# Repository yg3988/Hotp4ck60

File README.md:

# Hotp4ck 60 - 60% Layout Custom Keyboard Schematic & PCB

This keyboard PCB is a ANSI 60% Layout with Bluetooth 5.4 support using the [nRF52840](https://www.nordicsemi.com/products/nrf52840) chip produced by [Nordic Semiconductor](https://www.nordicsemi.com/).

## Features

* Supported Bluetooth
* USB Type-C
* 1000mAh Li-Po Battery
    * Battery Connector : MOLEX [51021-0200](https://www.molex.com/en-us/products/part-detail/510210200)
    * Battery Connector Socket : MOLEX [PicoBlade 53261-0271](https://www.molex.com/en-us/products/part-detail/532610271)
    * Note :
        * If you change the battery capacity, You MUST program the battery chargin current by replacing `R4` at this [Schematic](/Hotp4ck_Battery.kicad_sch) for safety.
* No LED per key 
* No Underglow LEDs
* Split Space-bar(1.25u + 2.75u + 2.25u)

## Schematic

* [PDF Schematic](misc/Hotp4ck60_schemetic.pdf)

## PCB

Generated by [InteractiveHtmlBom](https://github.com/openscopeproject/InteractiveHtmlBom) plugin for KiCad.

## Keyboard Layout

## Bootloader & Firmware

* [Bootloader](https://github.com/yg3988/Adafruit_nRF52_Bootloader/actions)
    * Download Bootloader from the Recently `Actions/Artifacts`

* [Firmware](https://github.com/yg3988/zmk-config/actions/runs/5494728345)
    * Download Firmware from the Recently `Actions/Artifacts`
 
## License
This keyboard PCB is licensed under the CERN Open Hardware Licence Version 2 - Permissive.

## References

* ### PCB Design : [zmk-designguide](https://github.com/ebastler/zmk-designguide) by [ebastler](https://github.com/ebastler)
* ### Firmware
    * ### ZMK : [zmk](https://github.com/zhiayang/zmk) by [zhiayang](https://github.com/zhiayang)
        > Source ZMK : zmkfirmware's [zmk](https://github.com/zmkfirmware/zmk)
    * ### [zmk-config](https://zmk.dev/docs/user-setup)
* ### Bootloader : [Adafruit_nRF52_Bootloader](https://github.com/adafruit/Adafruit_nRF52_Bootloader)

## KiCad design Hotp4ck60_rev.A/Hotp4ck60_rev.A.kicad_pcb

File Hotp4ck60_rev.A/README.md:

# Hotp4ck 60 - 60% Layout Custom Keyboard Schematic & PCB

This keyboard PCB is a ANSI 60% Layout with Bluetooth 5.4 support using the [nRF52840](https://www.nordicsemi.com/products/nrf52840) chip produced by [Nordic Semiconductor](https://www.nordicsemi.com/).

## Features

* Supported Bluetooth
* USB Type-C
* 1000mAh Li-Po Battery
    * Battery Connector : MOLEX [51021-0200](https://www.molex.com/en-us/products/part-detail/510210200)
    * Battery Connector Socket : MOLEX [PicoBlade 53261-0271](https://www.molex.com/en-us/products/part-detail/532610271)
    * Note :
        * If you change the battery capacity, You MUST program the battery chargin current by replacing `R4` at this [Schematic](/Hotp4ck_Battery.kicad_sch) for safety.
* No LED per key 
* No Underglow LEDs
* Split Space-bar(1.25u + 2.75u + 2.25u)

## Schematic

* [PDF Schematic](misc/Hotp4ck60_schemetic.pdf)

## PCB

Generated by [InteractiveHtmlBom](https://github.com/openscopeproject/InteractiveHtmlBom) plugin for KiCad.

## Keyboard Layout

## Bootloader & Firmware

* [Bootloader](https://github.com/yg3988/Adafruit_nRF52_Bootloader/actions)
    * Download Bootloader from the Recently `Actions/Artifacts`

* [Firmware](https://github.com/yg3988/zmk-config/actions/)
    * Download Firmware from the Recently `Actions/Artifacts`
 
## License
This keyboard PCB is licensed under the CERN Open Hardware Licence Version 2 - Permissive.

## References

* ### PCB Design : [zmk-designguide](https://github.com/ebastler/zmk-designguide) by [ebastler](https://github.com/ebastler)
* ### Firmware
    * ### ZMK : [zmk](https://github.com/zhiayang/zmk) by [zhiayang](https://github.com/zhiayang)
        > Source ZMK : zmkfirmware's [zmk](https://github.com/zmkfirmware/zmk)
    * ### [zmk-config](https://zmk.dev/docs/user-setup)
* ### Bootloader : [Adafruit_nRF52_Bootloader](https://github.com/adafruit/Adafruit_nRF52_Bootloader)

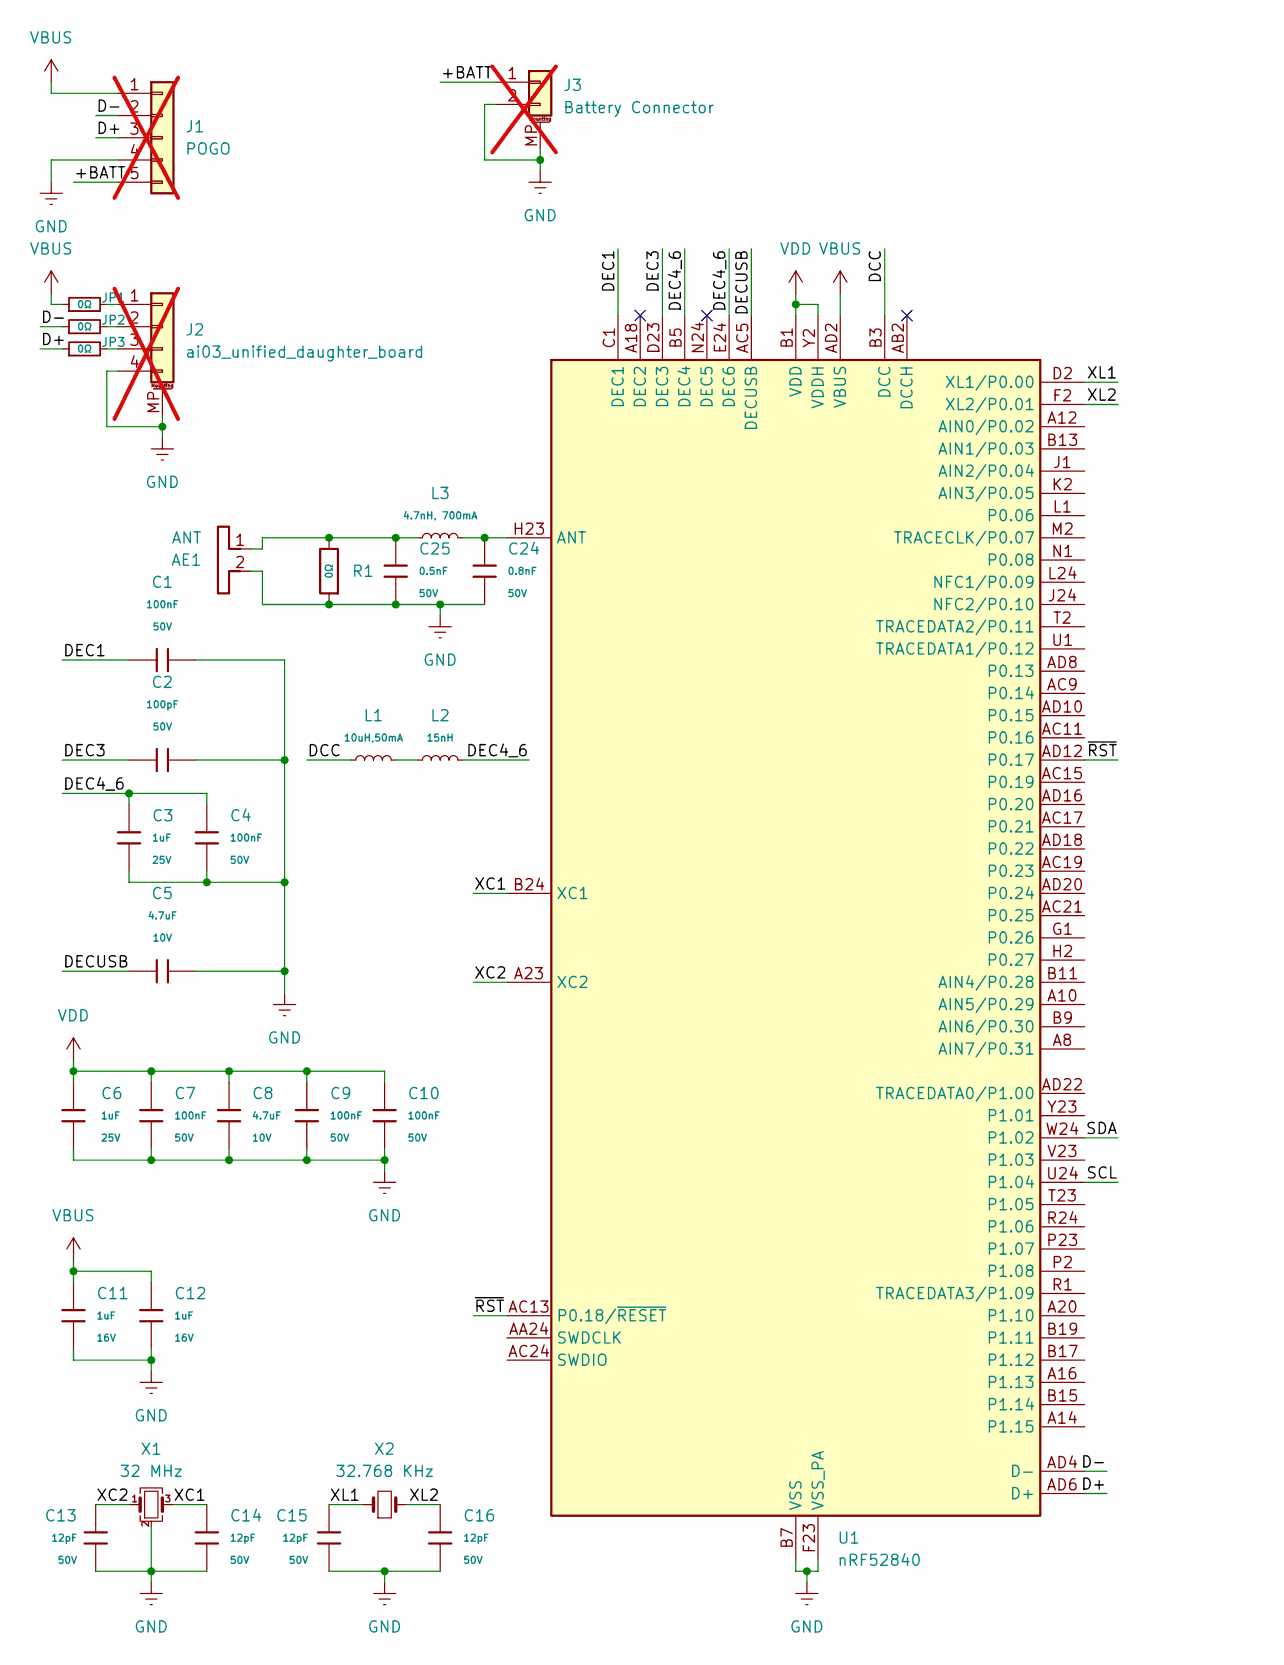
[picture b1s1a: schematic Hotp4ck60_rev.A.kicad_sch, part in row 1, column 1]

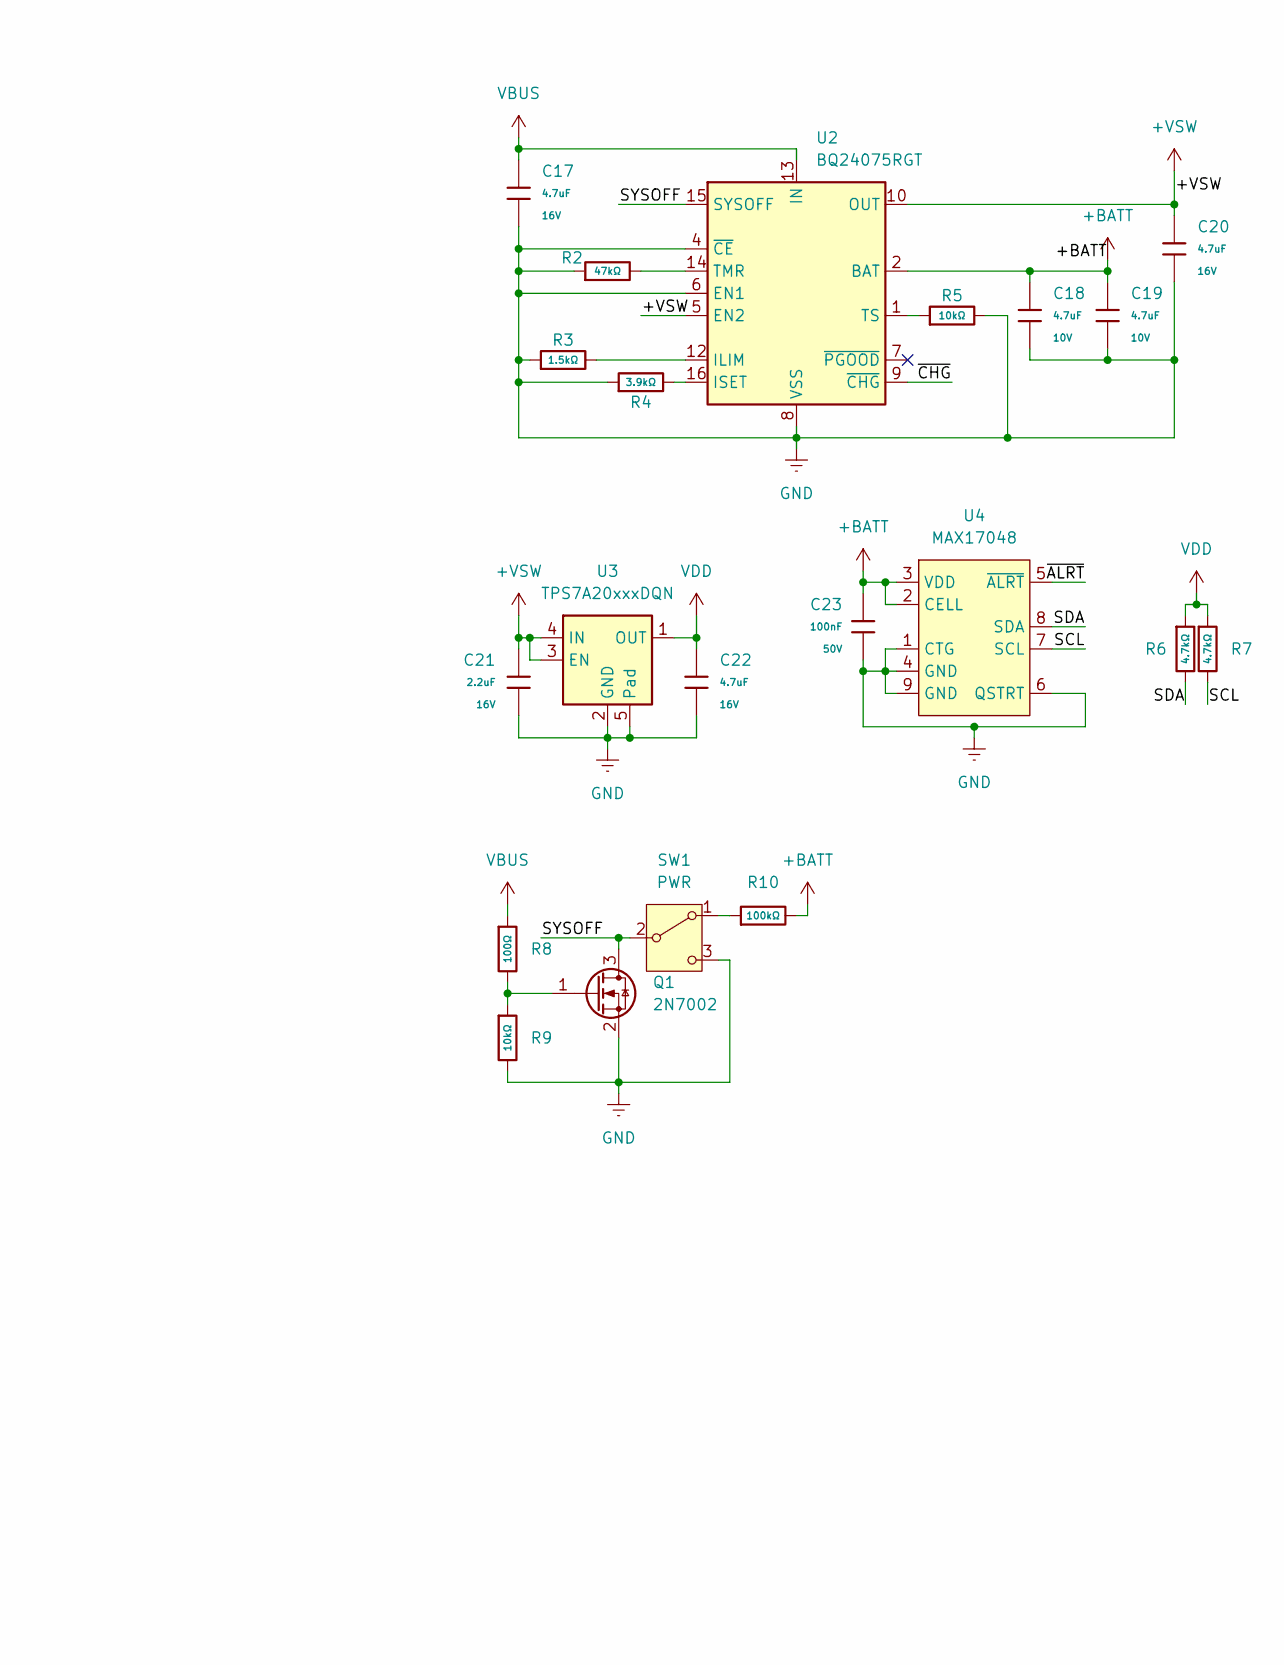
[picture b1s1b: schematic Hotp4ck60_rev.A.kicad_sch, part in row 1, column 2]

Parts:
AE1: ANT; Texas_SWRA117D_2.4GHz_Right
C1, C4, C7, C9, C10, C23: 100nF; C_0402_1005Metric; Voltage Rated 50V; Tolerance ±10%; Part CL05B104KB54PNC; LCSC C307331
C2: 100pF; C_0402_1005Metric; Voltage Rated 50V; Tolerance ±5%; Part 0402CG101J500NT; LCSC C1546
C3, C6: 1uF; C_0402_1005Metric; Voltage Rated 25V; Tolerance ±10%; Part CL05A105KA5NQNC; LCSC C52923
C5, C8, C18, C19: 4.7uF; C_0402_1005Metric; Voltage Rated 10V; Tolerance ±20%; Part CL05A475MP5NRNC; LCSC C23733
C11, C12: 1uF; C_0402_1005Metric; Voltage Rated 16V; Tolerance ±10%; Part CL10A105KO8NNNC; LCSC C1592
C13, C14, C15, C16: 12pF; C_0402_1005Metric; Voltage Rated 50V; Tolerance ±5%; Part 0402CG120J500NT; LCSC C1547
C17, C20, C22: 4.7uF; C_0603_1608Metric; Voltage Rated 16V; Tolerance ±10%; Part CL10A475KO8NNNC; LCSC C19666
C21: 2.2uF; C_0603_1608Metric; Voltage Rated 16V; Tolerance ±10%; Part CL10A225KO8NNNC; LCSC C23630
C24: 0.8nF; C_0402_1005Metric; Voltage Rated 50V; Tolerance ±0.05pF; Part GJM1555C1HR80WB01D; LCSC C88902
C25: 0.5nF; C_0402_1005Metric; Voltage Rated 50V; Tolerance ±0.1pF; Part CC0402BRNPO9BNR50; LCSC C309456
J1: POGO; PinHeader_1x05_P2.54mm_Vertical; not fitted
J2: ai03_unified_daughter_board; JST_SH_SM04B-SRSS-TB_1x04-1MP_P1.00mm_Horizontal; not fitted
J3: Battery Connector; Molex_PicoBlade_53261-0271_1x02-1MP_P1.25mm_Horizontal; not fitted
JP1, JP2, JP3: 0Ω; R_0201_0603Metric
L1: 10uH,50mA; L_0603_1608Metric; Tolerance ±20%; Part APQM18FN100M00D; LCSC C50325679
L2: 15nH; L_0402_1005Metric; Tolerance ±5%; Part VHF100505HQ15NJT; LCSC C395049
L3: 4.7nH, 700mA; L_0402_1005Metric; Tolerance ±0.3nH; Part VHF100505HQ4N7ST; LCSC C395070
Q1: 2N7002; SOT-23
R1: 0Ω; R_0402_1005Metric; Overload Voltage (Max) 50V; Tolerance ±1%; Part 0402WGF0000TCE; LCSC C17168
R2: 47kΩ; R_0402_1005Metric; Overload Voltage (Max) 50V; Tolerance ±1%; Part 0402WGF4702TCE; LCSC C25792
R3: 1.5kΩ; R_0402_1005Metric; Overload Voltage (Max) 50V; Tolerance ±1%; Part 0402WGF1501TCE; LCSC C25867
R4: 3.9kΩ; R_0402_1005Metric; Overload Voltage (Max) 50V; Tolerance ±1%; Part 0402WGF3901TCE; LCSC C51721
R5, R9: 10kΩ; R_0402_1005Metric; Overload Voltage (Max) 50V; Tolerance ±1%; Part 0402WGF1002TCE; LCSC C25744
R6, R7: 4.7kΩ; R_0402_1005Metric; Overload Voltage (Max) 50V; Tolerance ±1%; Part 0402WGF4701TCE; LCSC C25900
R8: 100Ω; R_0402_1005Metric; Overload Voltage (Max) 50V; Tolerance ±1%; Part 0402WGF1000TCE; LCSC C25076
R10: 100kΩ; R_0402_1005Metric; Overload Voltage (Max) 50V; Tolerance ±1%; Part 0402WGF1003TCE; LCSC C25741
SW1: PWR; SW-SMD_SHOUHAN_MST-22D18G23J_C2875122
U1: nRF52840; Nordic_AQFN-73-1EP_7x7mm_P0.5mm
U2: BQ24075RGT; VQFN-16-1EP_3x3mm_P0.5mm_EP1.6x1.6mm
U3: TPS7A20xxxDQN; Texas_X2SON-4_1x1mm_P0.65mm
U4: MAX17048; DFN-8-1EP_2x2mm_P0.5mm_EP0.6x1.2mm
X1: 32 MHz; Crystal_SMD_2016-4Pin_2.0x1.6mm
X2: 32.768 KHz; Crystal_SMD_2012-2Pin_2.0x1.2mm

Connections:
+BATT: C18.2, C19.2, C23.1, J1.5, J3.1, R10.2, U2.2 (BAT), U2.3 (BAT), U4.2 (CELL), U4.3 (VDD)
+VSW: C20.1, C21.1, U2.5 (EN2), U2.10 (OUT), U2.11 (OUT), U3.3 (EN), U3.4 (IN)
/D+: J1.3, JP3.1, U1.AD6 (D+)
/D-: J1.2, JP2.1, U1.AD4 (D-)
/DCC: L1.1, U1.B3 (DCC)
/DEC1: C1.1, U1.C1 (DEC1)
/DEC3: C2.1, U1.D23 (DEC3)
/DEC4_6: C3.1, C4.1, L2.2, U1.B5 (DEC4), U1.E24 (DEC6)
/DECUSB: C5.2, U1.AC5 (DECUSB)
/SCL: R7.2, U1.U24 (P1.04), U4.7 (SCL)
/SDA: R6.2, U1.W24 (P1.02), U4.8 (SDA)
/SYSOFF: Q1.3 (D), SW1.2 (B), U2.15 (SYSOFF)
/XC1: C14.1, U1.B24 (XC1), X1.3
/XC2: C13.1, U1.A23 (XC2), X1.1
/XL1: C15.1, U1.D2 (XL1/P0.00), X2.1
/XL2: C16.1, U1.F2 (XL2/P0.01), X2.2
/~ALRT: U4.5 (~ALRT)
/~CHG: U2.9 (~CHG)
/~RST: U1.AC13 (P0.18/~RESET), U1.AD12 (P0.17)
GND: AE1.2, C1.2, C2.2, C3.2, C4.2, C5.1, C6.1, C7.1, C8.1, C9.1, C10.1, C11.1, C12.1, C13.2, C14.2, C15.2, C16.2, C17.2, C18.1, C19.1, C20.2, C21.2, C22.2, C23.2, C24.1, C25.1, J1.4, J2.4, J2.MP (MountPin), J3.2, J3.MP (MountPin), Q1.2 (S), R1.1, R2.1, R3.1, R4.1, R5.2, R9.2, SW1.3 (C), U1.B7 (VSS), U1.EP (VSS), U1.F23 (VSS_PA), U2.4 (~CE), U2.6 (EN1), U2.8 (VSS), U2.17 (VSS), U3.2 (GND), U3.5 (Pad), U4.1 (CTG), U4.4 (GND), U4.6 (QSTRT), U4.9 (GND), X1.2 (G), X1.4 (G)
unnamed: AE1.1, C25.2, L3.1, R1.2
unnamed: J2.1, JP1.2
unnamed: J2.2, JP2.2
unnamed: J2.3, JP3.2
unnamed: L1.2, L2.1
unnamed: Q1.1 (G), R8.2, R9.1
unnamed: R10.1, SW1.1 (A)
unnamed: C24.2, L3.2, U1.H23 (ANT)
unnamed: R3.2, U2.12 (ILIM)
unnamed: R4.2, U2.16 (ISET)
unnamed: R2.2, U2.14 (TMR)
unnamed: R5.1, U2.1 (TS)
VBUS: C11.2, C12.2, C17.1, J1.1, JP1.1, R8.1, U1.AD2 (VBUS), U2.13 (IN)
VDD: C6.2, C7.2, C8.2, C9.2, C10.2, C22.1, R6.1, R7.1, U1.A22 (VDD), U1.AD14 (VDD), U1.AD23 (VDD), U1.B1 (VDD), U1.W1 (VDD), U1.Y2 (VDDH), U3.1 (OUT)

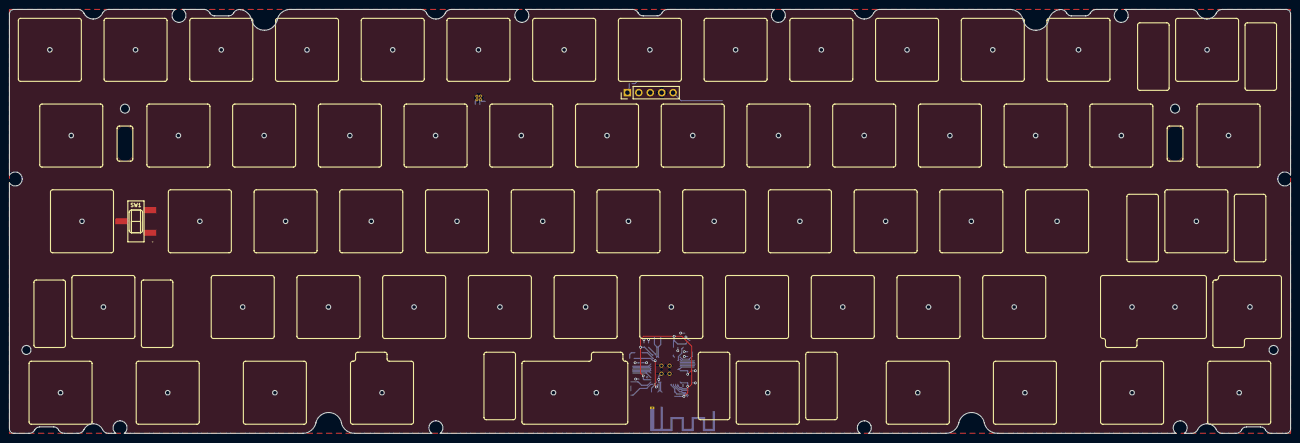
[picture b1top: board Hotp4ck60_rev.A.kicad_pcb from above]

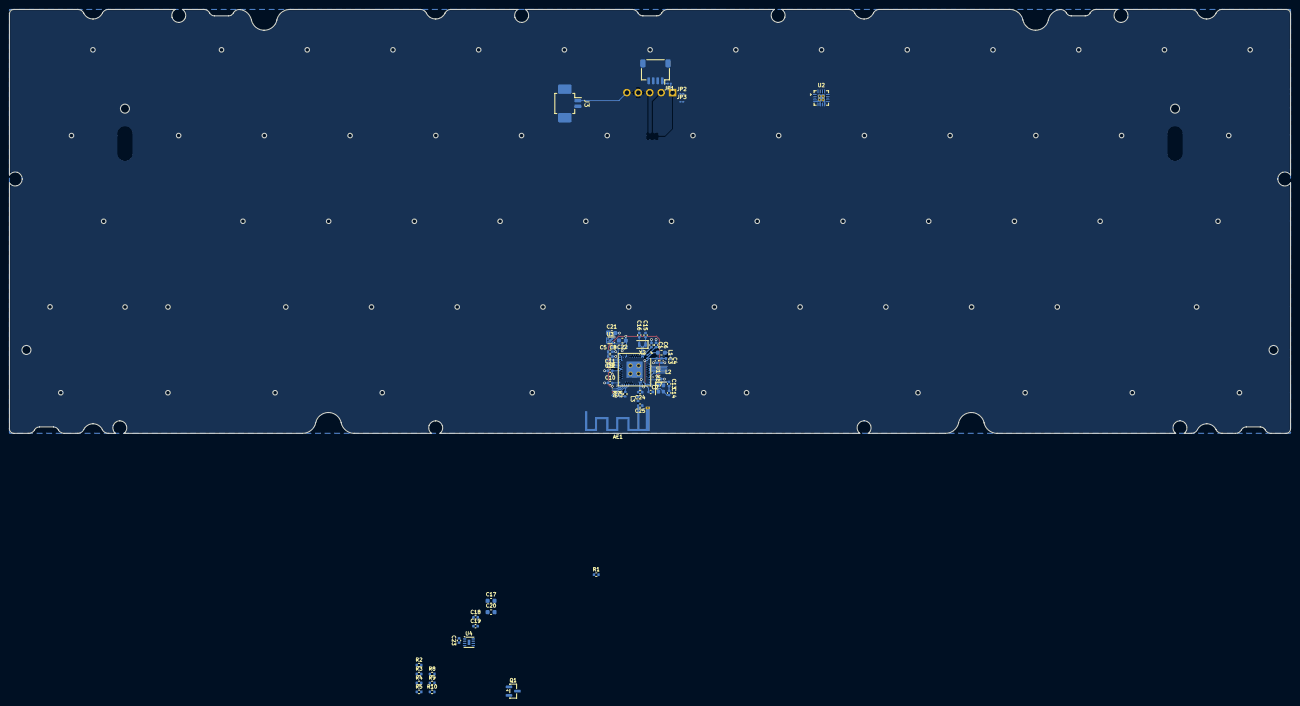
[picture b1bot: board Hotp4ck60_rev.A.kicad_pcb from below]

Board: 2 copper layers, 284.7 x 94.2 mm, 53 parts (51 on the bottom side), 32 nets.

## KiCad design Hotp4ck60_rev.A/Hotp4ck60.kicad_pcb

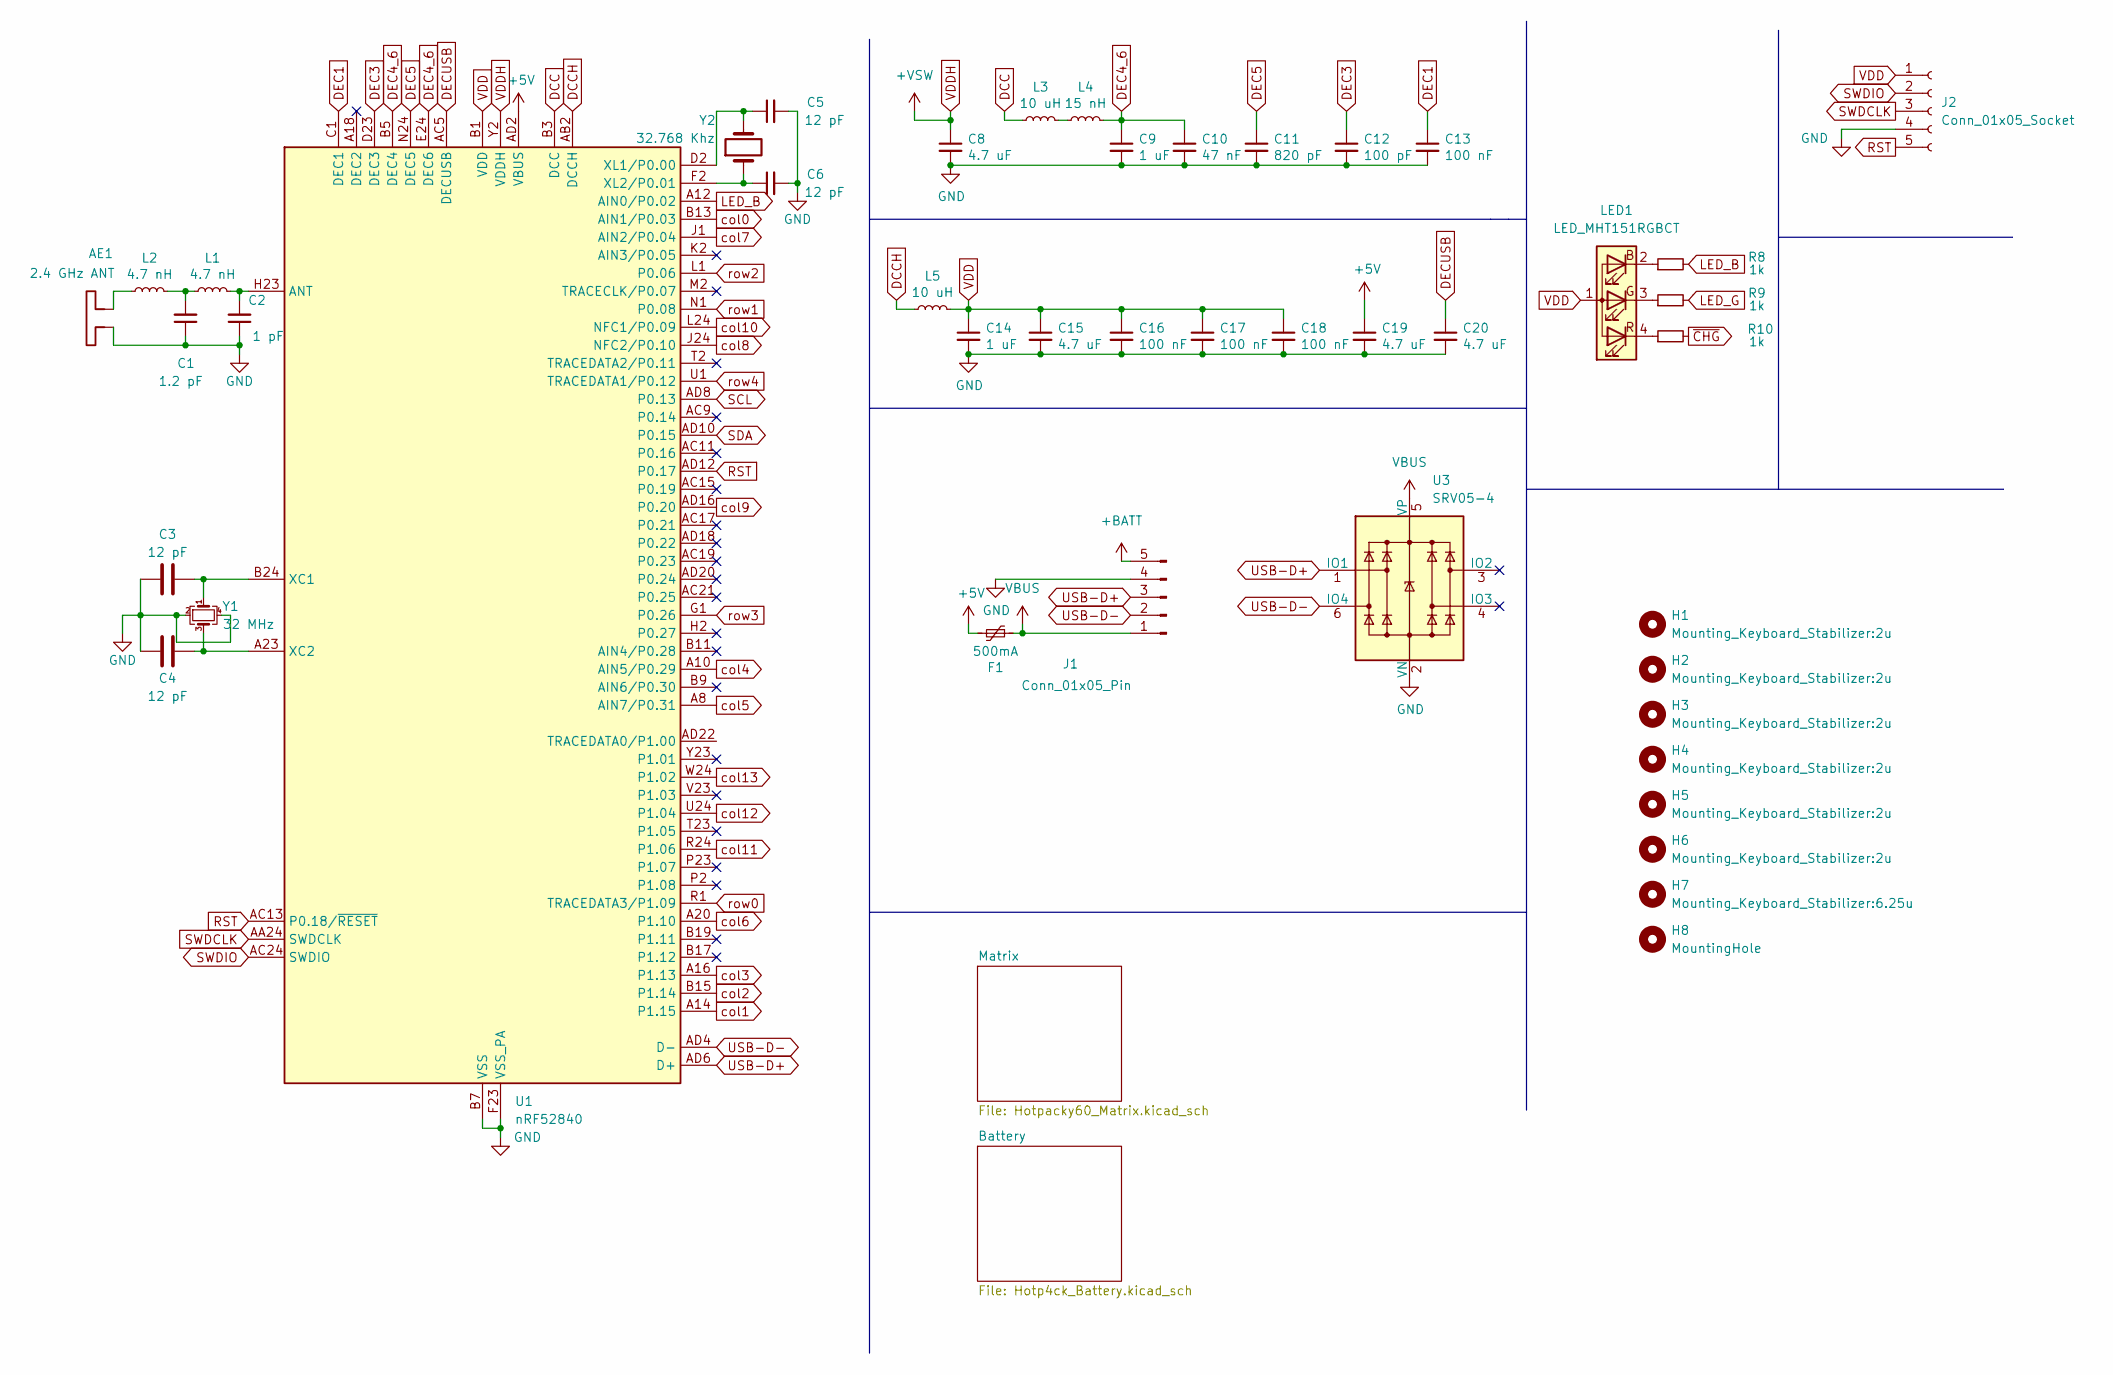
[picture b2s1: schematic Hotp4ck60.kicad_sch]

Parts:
AE1: 2.4 GHz ANT; Texas_SWRA117D_2.4GHz_Right
C1: 1.2 pF; C_0402_1005Metric; LCSC C327292
C2: 1 pF; C_0402_1005Metric; LCSC C309455
C3, C4, C5, C6: 12 pF; C_0402_1005Metric; LCSC C1547
C8, C15, C19, C20: 4.7 uF; C_0402_1005Metric; LCSC C23733
C9, C14: 1 uF; C_0402_1005Metric; LCSC C52923
C10: 47 nF; C_0603_1608Metric; LCSC C26403
C11: 820 pF; C_0402_1005Metric; LCSC C161159
C12: 100 pF; C_0402_1005Metric; LCSC C1546
C13, C16, C17, C18: 100 nF; C_0402_1005Metric; LCSC C1525
F1: 500mA; Fuse_0603_1608Metric; LCSC C883095
H1, H2, H3, H4, H5, H6: Mounting_Keyboard_Stabilizer:2u; Stabilizer_Cherry_MX_2u
H7: Mounting_Keyboard_Stabilizer:6.25u; Stabilizer_Cherry_MX_6.25u
H8: MountingHole; Neo60_2
J1: Conn_01x05_Pin; PinHeader_1x05_P2.54mm_Vertical
J2: Conn_01x05_Socket; PinSocket_1x05_P2.54mm_Vertical
L1: 4.7 nH; L_0402_1005Metric; LCSC C251965
L2: 4.7 nH; L_0402_1005Metric; LCSC C136252
L3, L5: 10 uH; L_0603_1608Metric; LCSC C252081
L4: 15 nH; L_0402_1005Metric; LCSC C329619
LED1: LED_MHT151RGBCT; LED_1206R
R8, R9, R10: 1k; R_0402_1005Metric; LCSC C25890
U1: nRF52840; Nordic_AQFN-73-1EP_7x7mm_P0.5mm; LCSC C190794
U3: SRV05-4; SOT-23-6-routable; LCSC C7420376
Y1: 32 MHz; Crystal_SMD_2016-4Pin_2.0x1.6mm; LCSC C2149125
Y2: 32.768 Khz; Crystal_SMD_2012-2Pin_2.0x1.2mm; LCSC C55208

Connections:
+5V: C19.1, F1.2, U1.AD2 (VBUS); also elsewhere on the board
+BATT: J1.5; also elsewhere on the board
DCC: L3.1, U1.B3 (DCC)
DCCH: L5.1, U1.AB2 (DCCH)
DEC1: C13.1, U1.C1 (DEC1)
DEC3: C12.1, U1.D23 (DEC3)
DEC4_6: C9.1, C10.1, L4.2, U1.B5 (DEC4), U1.E24 (DEC6)
DEC5: C11.1, U1.N24 (DEC5)
DECUSB: C20.1, U1.AC5 (DECUSB)
GND: AE1.2, C1.1, C2.1, C3.1, C4.2, C5.2, C6.2, C8.2, C9.2, C10.2, C11.2, C12.2, C13.2, C14.2, C15.2, C16.2, C17.2, C18.2, C19.2, C20.2, J1.4, J2.4, U1.B7 (VSS), U1.EP (VSS), U1.F23 (VSS_PA), U3.2 (VN), Y1.2, Y1.4; also elsewhere on the board
LED_B: R8.2, U1.A12 (AIN0/P0.02)
LED_G: R9.2
unnamed: AE1.1, L2.1
unnamed: C1.2, L1.1, L2.2
unnamed: L3.2, L4.1
unnamed: LED1.2 (BK), R8.1
unnamed: LED1.3 (GK), R9.1
unnamed: LED1.4 (RK), R10.1
unnamed: C2.2, L1.2, U1.H23 (ANT)
unnamed: C3.2, U1.B24 (XC1), Y1.1
unnamed: C4.1, U1.A23 (XC2), Y1.3
unnamed: C5.1, U1.D2 (XL1/P0.00), Y2.2
unnamed: C6.1, U1.F2 (XL2/P0.01), Y2.1
RST: J2.5, U1.AC13 (P0.18/~RESET), U1.AD12 (P0.17)
SCL: U1.AD8 (P0.13); also elsewhere on the board
SDA: U1.AD10 (P0.15); also elsewhere on the board
SWDCLK: J2.3, U1.AA24 (SWDCLK)
SWDIO: J2.2, U1.AC24 (SWDIO)
USB-D+: J1.3, U1.AD6 (D+), U3.1 (IO1)
USB-D-: J1.2, U1.AD4 (D-), U3.6 (IO4)
VBUS: F1.1, J1.1, U3.5 (VP)
VDD: C14.1, C15.1, C16.1, C17.1, C18.1, J2.1, L5.2, LED1.1 (A), U1.A22 (VDD), U1.AD14 (VDD), U1.AD23 (VDD), U1.B1 (VDD), U1.W1 (VDD); also elsewhere on the board
VDDH: C8.1, U1.Y2 (VDDH); also elsewhere on the board
col0: U1.B13 (AIN1/P0.03); also elsewhere on the board
col1: U1.A14 (P1.15); also elsewhere on the board
col2: U1.B15 (P1.14); also elsewhere on the board
col3: U1.A16 (P1.13); also elsewhere on the board
col4: U1.A10 (AIN5/P0.29); also elsewhere on the board
col5: U1.A8 (AIN7/P0.31); also elsewhere on the board
col6: U1.A20 (P1.10); also elsewhere on the board
col7: U1.J1 (AIN2/P0.04); also elsewhere on the board
col8: U1.J24 (NFC2/P0.10); also elsewhere on the board
col9: U1.AD16 (P0.20); also elsewhere on the board
col10: U1.L24 (NFC1/P0.09); also elsewhere on the board
col11: U1.R24 (P1.06); also elsewhere on the board
col12: U1.U24 (P1.04); also elsewhere on the board
col13: U1.W24 (P1.02); also elsewhere on the board
row0: U1.R1 (TRACEDATA3/P1.09); also elsewhere on the board
row1: U1.N1 (P0.08); also elsewhere on the board
row2: U1.L1 (P0.06); also elsewhere on the board
row3: U1.G1 (P0.26); also elsewhere on the board
row4: U1.U1 (TRACEDATA1/P0.12); also elsewhere on the board
~CHG: R10.2; also elsewhere on the board

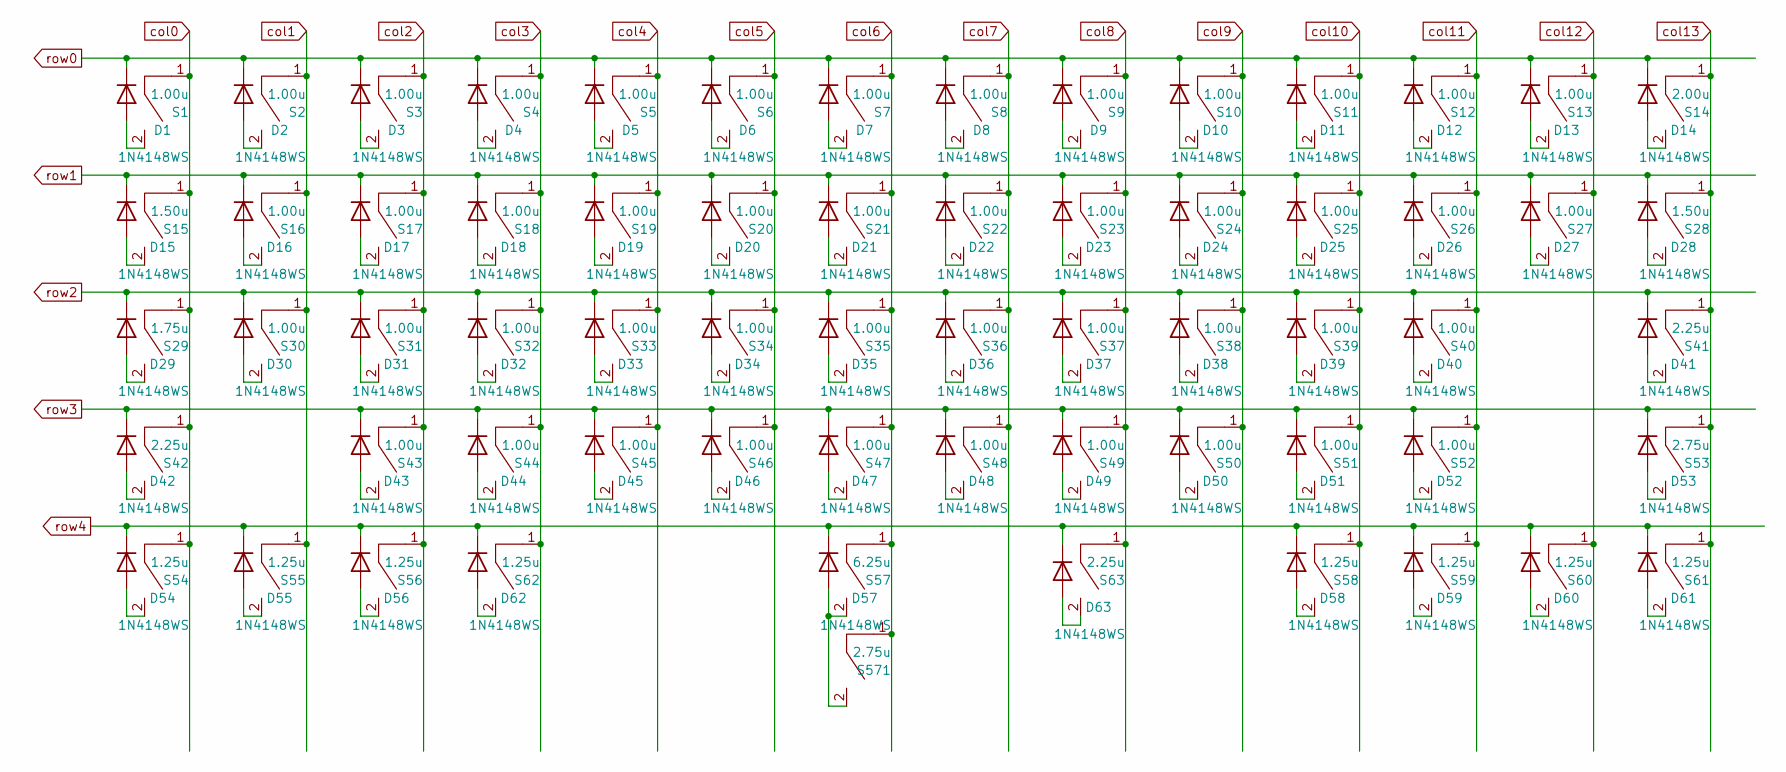
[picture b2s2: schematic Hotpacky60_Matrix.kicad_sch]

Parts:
D1, D2, D3, D4, D5, D6, D7, D8, D9, D10, D11, D12, D13, D14, D15, D16, D17, D18, D19, D20, D21, D22, D23, D24, D25, D26, D27, D28, D29, D30, D31, D32, D33, D34, D35, D36, D37, D38, D39, D40, D41, D42, D43, D44, D45, D46, D47, D48, D49, D50, D51, D52, D53, D54, D55, D56, D57, D58, D59, D60, D61, D62, D63: 1N4148WS; D_SOD-323
S1, S2, S3, S4, S5, S6, S7, S8, S9, S10, S11, S12, S13, S16, S17, S18, S19, S20, S21, S22, S23, S24, S25, S26, S27, S30, S31, S32, S33, S34, S35, S36, S37, S38, S39, S40, S43, S44, S45, S46, S47, S48, S49, S50, S51, S52: 1.00u; SW_Cherry_MX_PCB_1.00u
S14: 2.00u; SW_Cherry_MX_PCB_2.00u
S15, S28: 1.50u; SW_Cherry_MX_PCB_1.50u
S29: 1.75u; SW_Cherry_MX_PCB_1.75u
S41, S42, S63: 2.25u; SW_Cherry_MX_PCB_2.25u
S53, S571: 2.75u; SW_Cherry_MX_PCB_2.75u
S54, S55, S56, S58, S59, S60, S61, S62: 1.25u; SW_Cherry_MX_PCB_1.25u
S57: 6.25u; SW_Cherry_MX_PCB_6.25u

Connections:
unnamed: D1.2 (A), S1.2
unnamed: D2.2 (A), S2.2
unnamed: D3.2 (A), S3.2
unnamed: D4.2 (A), S4.2
unnamed: D5.2 (A), S5.2
unnamed: D6.2 (A), S6.2
unnamed: D7.2 (A), S7.2
unnamed: D8.2 (A), S8.2
unnamed: D9.2 (A), S9.2
unnamed: D10.2 (A), S10.2
unnamed: D11.2 (A), S11.2
unnamed: D12.2 (A), S12.2
unnamed: D13.2 (A), S13.2
unnamed: D14.2 (A), S14.2
unnamed: D15.2 (A), S15.2
unnamed: D16.2 (A), S16.2
unnamed: D17.2 (A), S17.2
unnamed: D18.2 (A), S18.2
unnamed: D19.2 (A), S19.2
unnamed: D20.2 (A), S20.2
unnamed: D21.2 (A), S21.2
unnamed: D22.2 (A), S22.2
unnamed: D23.2 (A), S23.2
unnamed: D24.2 (A), S24.2
unnamed: D25.2 (A), S25.2
unnamed: D26.2 (A), S26.2
unnamed: D27.2 (A), S27.2
unnamed: D28.2 (A), S28.2
unnamed: D29.2 (A), S29.2
unnamed: D30.2 (A), S30.2
unnamed: D31.2 (A), S31.2
unnamed: D32.2 (A), S32.2
unnamed: D33.2 (A), S33.2
unnamed: D34.2 (A), S34.2
unnamed: D35.2 (A), S35.2
unnamed: D36.2 (A), S36.2
unnamed: D37.2 (A), S37.2
unnamed: D38.2 (A), S38.2
unnamed: D39.2 (A), S39.2
unnamed: D40.2 (A), S40.2
unnamed: D41.2 (A), S41.2
unnamed: D42.2 (A), S42.2
unnamed: D43.2 (A), S43.2
unnamed: D44.2 (A), S44.2
unnamed: D45.2 (A), S45.2
unnamed: D46.2 (A), S46.2
unnamed: D47.2 (A), S47.2
unnamed: D48.2 (A), S48.2
unnamed: D49.2 (A), S49.2
unnamed: D50.2 (A), S50.2
unnamed: D51.2 (A), S51.2
unnamed: D52.2 (A), S52.2
unnamed: D53.2 (A), S53.2
unnamed: D54.2 (A), S54.2
unnamed: D55.2 (A), S55.2
unnamed: D56.2 (A), S56.2
unnamed: D57.2 (A), S57.2, S571.2
unnamed: D58.2 (A), S58.2
unnamed: D59.2 (A), S59.2
unnamed: D60.2 (A), S60.2
unnamed: D61.2 (A), S61.2
unnamed: D62.2 (A), S62.2
unnamed: D63.2 (A), S63.2
col0: S1.1, S15.1, S29.1, S42.1, S54.1; also elsewhere on the board
col1: S2.1, S16.1, S30.1, S55.1; also elsewhere on the board
col2: S3.1, S17.1, S31.1, S43.1, S56.1; also elsewhere on the board
col3: S4.1, S18.1, S32.1, S44.1, S62.1; also elsewhere on the board
col4: S5.1, S19.1, S33.1, S45.1; also elsewhere on the board
col5: S6.1, S20.1, S34.1, S46.1; also elsewhere on the board
col6: S7.1, S21.1, S35.1, S47.1, S57.1, S571.1; also elsewhere on the board
col7: S8.1, S22.1, S36.1, S48.1; also elsewhere on the board
col8: S9.1, S23.1, S37.1, S49.1, S63.1; also elsewhere on the board
col9: S10.1, S24.1, S38.1, S50.1; also elsewhere on the board
col10: S11.1, S25.1, S39.1, S51.1, S58.1; also elsewhere on the board
col11: S12.1, S26.1, S40.1, S52.1, S59.1; also elsewhere on the board
col12: S13.1, S27.1, S60.1; also elsewhere on the board
col13: S14.1, S28.1, S41.1, S53.1, S61.1; also elsewhere on the board
row0: D1.1 (K), D2.1 (K), D3.1 (K), D4.1 (K), D5.1 (K), D6.1 (K), D7.1 (K), D8.1 (K), D9.1 (K), D10.1 (K), D11.1 (K), D12.1 (K), D13.1 (K), D14.1 (K); also elsewhere on the board
row1: D15.1 (K), D16.1 (K), D17.1 (K), D18.1 (K), D19.1 (K), D20.1 (K), D21.1 (K), D22.1 (K), D23.1 (K), D24.1 (K), D25.1 (K), D26.1 (K), D27.1 (K), D28.1 (K); also elsewhere on the board
row2: D29.1 (K), D30.1 (K), D31.1 (K), D32.1 (K), D33.1 (K), D34.1 (K), D35.1 (K), D36.1 (K), D37.1 (K), D38.1 (K), D39.1 (K), D40.1 (K), D41.1 (K); also elsewhere on the board
row3: D42.1 (K), D43.1 (K), D44.1 (K), D45.1 (K), D46.1 (K), D47.1 (K), D48.1 (K), D49.1 (K), D50.1 (K), D51.1 (K), D52.1 (K), D53.1 (K); also elsewhere on the board
row4: D54.1 (K), D55.1 (K), D56.1 (K), D57.1 (K), D58.1 (K), D59.1 (K), D60.1 (K), D61.1 (K), D62.1 (K), D63.1 (K); also elsewhere on the board

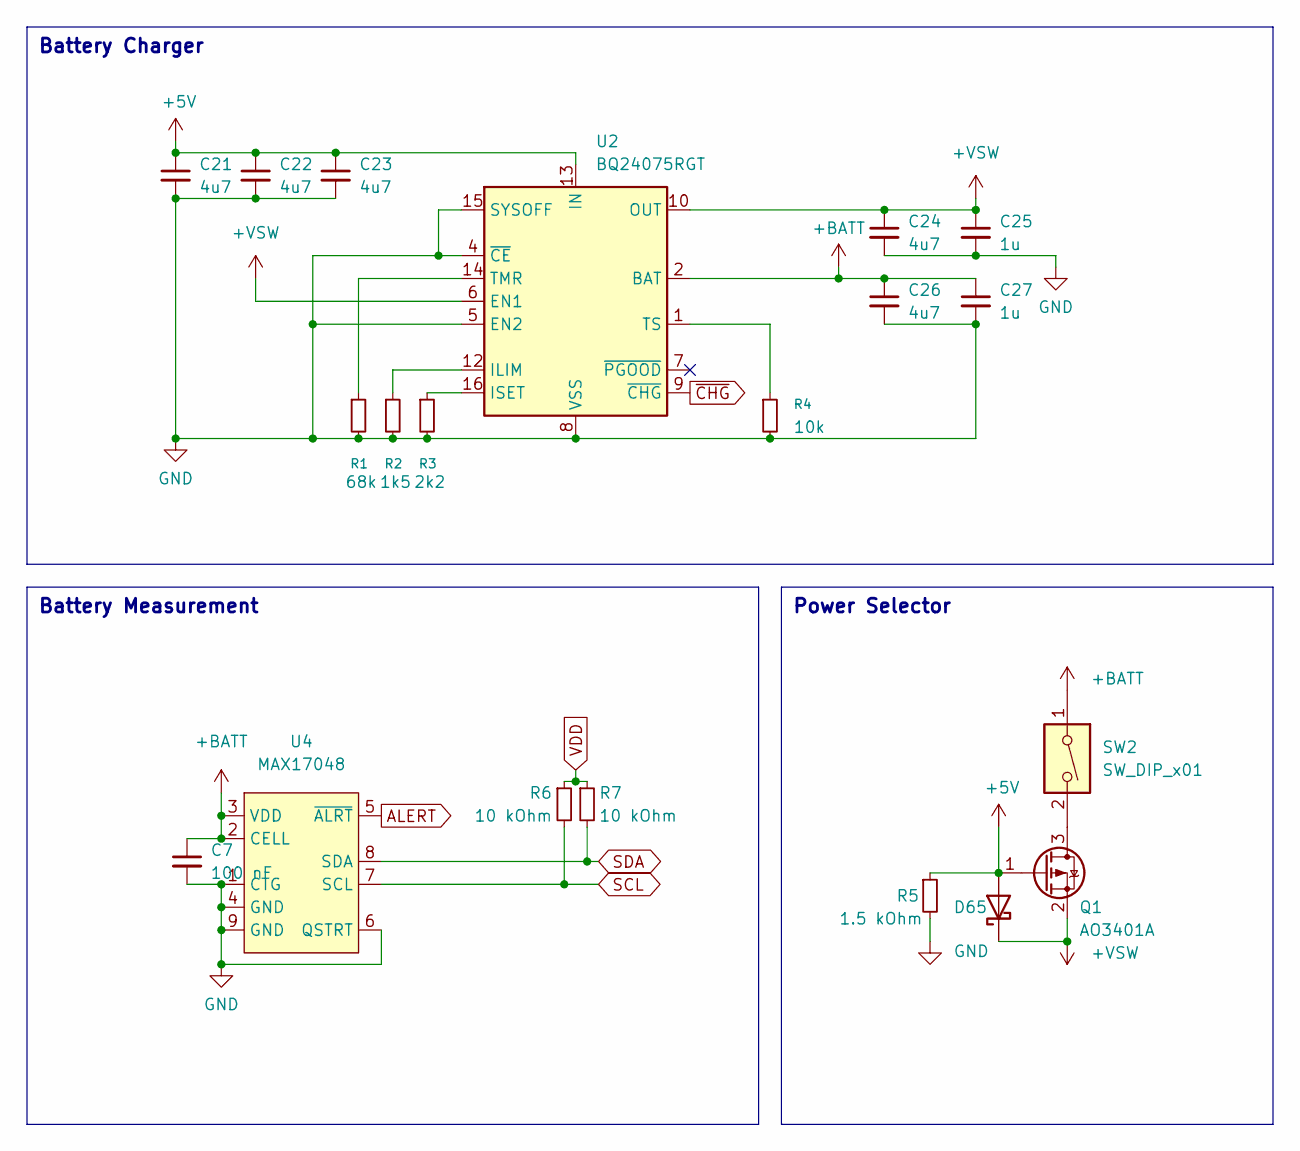
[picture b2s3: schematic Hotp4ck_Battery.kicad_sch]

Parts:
C7: 100 nF; C_0402_1005Metric
C21, C22, C23, C24, C26: 4u7; C_0402_1005Metric; LCSC C23733
C25, C27: 1u; C_0402_1005Metric; LCSC C52923
D65: D_Schottky; D_SOD-123
Q1: AO3401A; SOT-23
R1: 68k; R_0805_2012Metric; LCSC C17801
R2: 1k5; R_0402_1005Metric; LCSC C25867
R3: 2k2; R_0402_1005Metric; LCSC C25879
R4: 10k; R_0402_1005Metric; LCSC C25744
R5: 1.5 kOhm; R_0402_1005Metric; LCSC C25867
R6, R7: 10 kOhm; R_0402_1005Metric; LCSC C25744
SW2: SW_DIP_x01; SW_DIP_HOTP4CK
U2: BQ24075RGT; VQFN-16-1EP_3x3mm_P0.5mm_EP1.6x1.6mm
U4: MAX17048; DFN-8-1EP_2x2mm_P0.5mm_EP0.7x1.3mm

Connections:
+5V: C21.1, C22.1, C23.1, D65.2 (A), Q1.1 (G), R5.1, U2.13 (IN); also elsewhere on the board
+BATT: C7.1, C26.1, C27.1, SW2.1, U2.2 (BAT), U2.3 (BAT), U4.2 (CELL), U4.3 (VDD); also elsewhere on the board
ALERT: U4.5 (~ALRT)
GND: C7.2, C21.2, C22.2, C23.2, C24.2, C25.2, C26.2, C27.2, R1.2, R2.2, R3.2, R4.2, R5.2, U2.4 (~CE), U2.5 (EN2), U2.8 (VSS), U2.15 (SYSOFF), U2.17 (VSS), U4.1 (CTG), U4.4 (GND), U4.6 (QSTRT), U4.9 (GND); also elsewhere on the board
unnamed: Q1.3 (D), SW2.2
unnamed: R2.1, U2.12 (ILIM)
unnamed: R3.1, U2.16 (ISET)
unnamed: R1.1, U2.14 (TMR)
unnamed: R4.1, U2.1 (TS)
SCL: R6.2, U4.7 (SCL); also elsewhere on the board
SDA: R7.2, U4.8 (SDA); also elsewhere on the board
VDD: R6.1, R7.1; also elsewhere on the board
VDDH: C24.1, C25.1, D65.1 (K), Q1.2 (S), U2.6 (EN1), U2.10 (OUT), U2.11 (OUT); also elsewhere on the board
~CHG: U2.9 (~CHG); also elsewhere on the board

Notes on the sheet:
Battery Charger
Battery Measurement
Power Selector

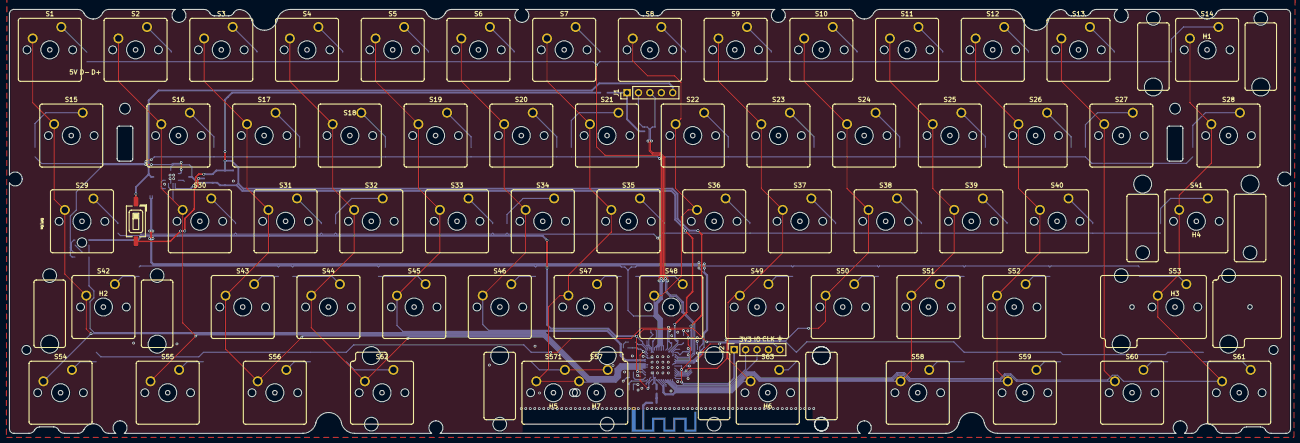
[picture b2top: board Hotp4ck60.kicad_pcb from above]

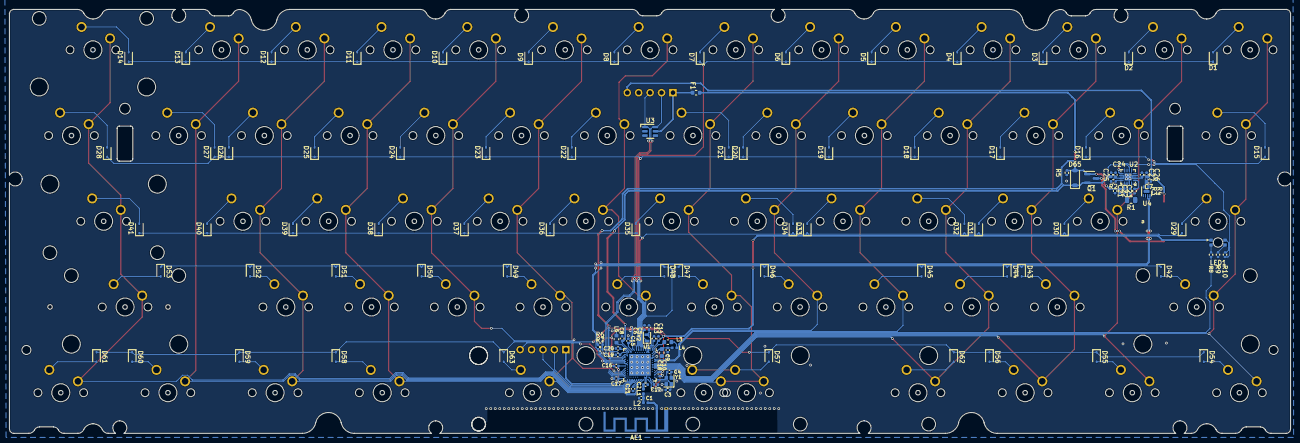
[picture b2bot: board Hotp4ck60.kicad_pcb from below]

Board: 2 copper layers, 284.7 x 94.2 mm, 191 parts (116 on the bottom side), 120 nets.
